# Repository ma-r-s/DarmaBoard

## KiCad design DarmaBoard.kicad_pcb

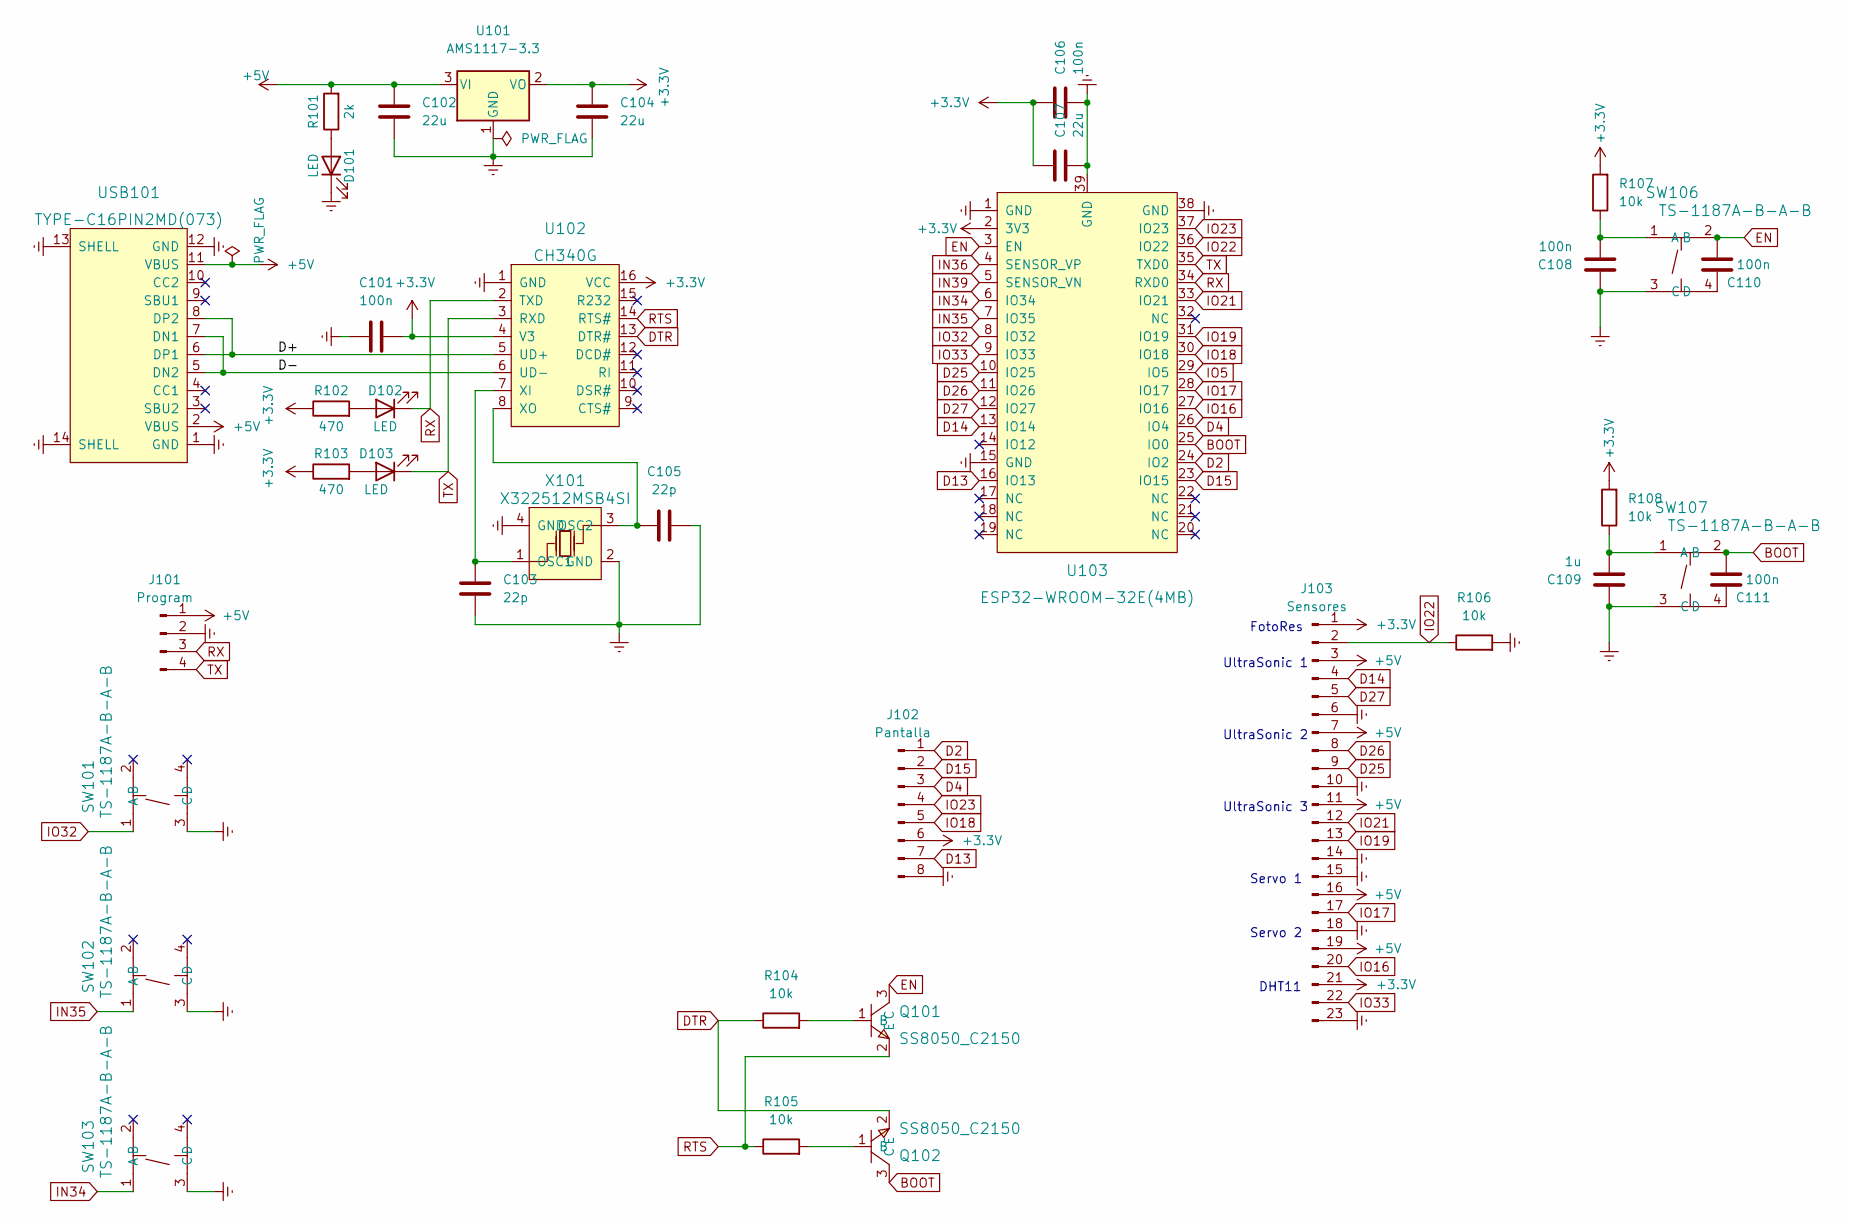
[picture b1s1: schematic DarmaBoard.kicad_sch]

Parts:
C101, C106, C108, C110, C111: 100n; C_0805_2012Metric
C102, C104, C107: 22u; C_0805_2012Metric
C103, C105: 22p; C_0805_2012Metric
C109: 1u; C_0805_2012Metric
D101, D102, D103: LED; LED_0805_2012Metric
J101: Program; PinSocket_1x04_P2.54mm_Vertical
J102: Pantalla; PinSocket_1x08_P2.54mm_Vertical
J103: Sensores; PinHeader_1x23_P2.54mm_Horizontal
Q101, Q102: SS8050_C2150; SOT-23-3_L2.9-W1.3-P1.90-LS2.4-BR; LCSC Part C2150
R101: 2k; R_0805_2012Metric
R102, R103: 470; R_0805_2012Metric
R104, R105, R106, R107, R108: 10k; R_0805_2012Metric
SW101, SW102, SW103, SW106, SW107: TS-1187A-B-A-B; SW-SMD_4P-L5.1-W5.1-P3.70-LS6.5-TL-2; LCSC Part C318884
U101: AMS1117-3.3; SOT-223-3_TabPin2
U102: CH340G; SOIC-16_L9.9-W3.9-P1.27-LS6.0-BL; LCSC Part C14267
U103: ESP32-WROOM-32E(4MB); WIFI-SMD_ESP32-WROOM-32E; LCSC Part C701341
USB101: TYPE-C16PIN2MD(073); USB-C-SMD_TYPE-C-6PIN-2MD-073; LCSC Part C2765186
X101: X322512MSB4SI; OSC-SMD_4P-L3.2-W2.5-BL; LCSC Part C9002

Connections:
+3V3: C101.2, C104.2, C106.1, C107.1, J102.6, J103.1, J103.21, R102.1, R103.1, R107.2, R108.2, U101.2 (VO), U102.4 (V3), U102.16 (VCC), U103.2 (3V3)
+5V: C102.2, J101.1, J103.3, J103.7, J103.11, J103.16, J103.19, R101.2, U101.3 (VI), USB101.2 (VBUS), USB101.11 (VBUS)
/D+: U102.5 (UD+), USB101.6 (DP1), USB101.8 (DP2)
/D-: U102.6 (UD-), USB101.5 (DN2), USB101.7 (DN1)
BOOT: C111.2, Q102.3 (C), SW107.2 (B), U103.25 (IO0)
D2: J102.1, U103.24 (IO2)
D4: J102.3, U103.26 (IO4)
D13: J102.7, U103.16 (IO13)
D14: J103.4, U103.13 (IO14)
D15: J102.2, U103.23 (IO15)
D25: J103.9, U103.10 (IO25)
D26: J103.8, U103.11 (IO26)
D27: J103.5, U103.12 (IO27)
DTR: Q102.2 (E), R104.1, U102.13 (DTR#)
EN: C110.2, Q101.3 (C), SW106.2 (B), U103.3 (EN)
Earth: C101.1, C102.1, C103.2, C104.1, C105.2, C106.2, C107.2, C108.1, C109.1, D101.1 (K), J101.2, J102.8, J103.6, J103.10, J103.14, J103.15, J103.18, J103.23, R106.2, SW101.3 (C), SW102.3 (C), SW103.3 (C), SW106.3 (C), SW107.3 (C), U101.1 (GND), U102.1 (GND), U103.1 (GND), U103.15 (GND), U103.38 (GND), U103.39 (GND), USB101.1 (GND), USB101.12 (GND), USB101.13 (SHELL), USB101.14 (SHELL), X101.2 (GND), X101.4 (GND)
IN34: SW103.1 (A), U103.6 (IO34)
IN35: SW102.1 (A), U103.7 (IO35)
IN36: U103.4 (SENSOR_VP)
IN39: U103.5 (SENSOR_VN)
IO5: U103.29 (IO5)
IO16: J103.20, U103.27 (IO16)
IO17: J103.17, U103.28 (IO17)
IO18: J102.5, U103.30 (IO18)
IO19: J103.13, U103.31 (IO19)
IO21: J103.12, U103.33 (IO21)
IO22: J103.2, R106.1, U103.36 (IO22)
IO23: J102.4, U103.37 (IO23)
IO32: SW101.1 (A), U103.8 (IO32)
IO33: J103.22, U103.9 (IO33)
unnamed: C103.1, U102.7 (XI), X101.1 (OSC1)
unnamed: C105.1, U102.8 (XO), X101.3 (OSC2)
unnamed: C108.2, R107.1, SW106.1 (A)
unnamed: C109.2, R108.1, SW107.1 (A)
unnamed: C110.1, SW106.4 (D)
unnamed: C111.1, SW107.4 (D)
unnamed: D101.2 (A), R101.1
unnamed: D102.2 (A), R102.2
unnamed: D103.2 (A), R103.2
unnamed: Q101.1 (B), R104.2
unnamed: Q102.1 (B), R105.2
RTS: Q101.2 (E), R105.1, U102.14 (RTS#)
RX: D102.1 (K), J101.3, U102.2 (TXD), U103.34 (RXD0)
TX: D103.1 (K), J101.4, U102.3 (RXD), U103.35 (TXD0)

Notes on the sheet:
UltraSonic 1
Servo 1
Servo 2
UltraSonic 2
FotoRes
UltraSonic 3
DHT11

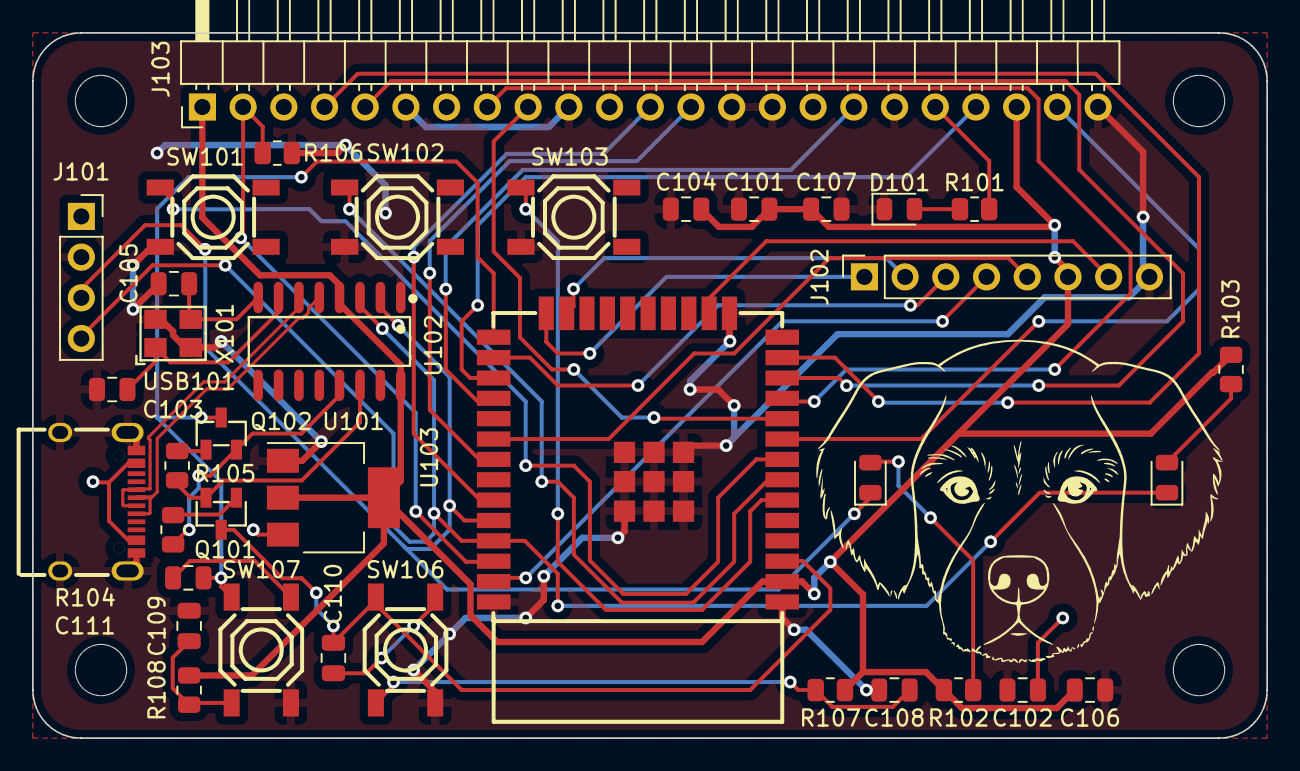
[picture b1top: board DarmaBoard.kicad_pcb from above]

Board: 2 copper layers, 77.0 x 44.0 mm, 37 parts (0 on the bottom side), 41 nets.
